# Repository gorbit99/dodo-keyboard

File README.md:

# Dodo

Dodo is a 60%, low-profile, wireless mechanical keyboard with per-key RGB
backlighting a display and a rotary encoder.

## BOM

To build the PCB, you will need the following components for each side (so make
sure to get double of each):

| Part                              | Count | Link                                                                |
| --------------------------------- | ----: | ------------------------------------------------------------------- |
| B5817W Diode                      |     1 | [AliExpress](https://www.aliexpress.com/item/1005005615035910.html) |
| SK6812 MINI-E <sup>1</sup>        |    30 | [AliExpress](https://www.aliexpress.com/item/1005005248164351.html) |
| 1N4148 SOD-123                    |    30 | [AliExpress](https://www.aliexpress.com/item/1005005271390029.html) |
| SMD 3.5 mm jack <sup>2</sup>      |     1 | [AliExpress](https://www.aliexpress.com/item/4000661908135.html)    |
| 2 pin POGO connector <sup>2</sup> |     1 | [AliExpress](https://www.aliexpress.com/item/1005002006325514.html) |
| AO3401A <sup>1</sup>              |     2 | [AliExpress](https://www.aliexpress.com/item/4001197981239.html)    |
| 2N7002 <sup>1</sup>               |     1 | [AliExpress](https://www.aliexpress.com/item/1005004759627915.html) |
| 10k Ω 0603 resistor <sup>1</sup>  |     3 | [AliExpress](https://www.aliexpress.com/item/1005006142628179.html) |
| 560 Ω 0603 resistor <sup>1</sup>  |     2 | [AliExpress](https://www.aliexpress.com/item/1005006142628179.html) |
| Momentary tactile switch          |     2 | [AliExpress](https://www.aliexpress.com/item/1005004159746274.html) |
| EC11E style encoder <sup>3</sup>  |     1 | [AliExpress](https://www.aliexpress.com/item/1005002358274622.html) |
| Kailh Choc V1                     |    30 | [AliExpress](https://www.aliexpress.com/item/1005004522163996.html) |
| XIAO BLE <sup>4</sup>             |     1 | [AliExpress](https://www.aliexpress.com/item/1005004459618789.html) |
| MCP23S17SS                        |     1 | [AliExpress](https://www.aliexpress.com/item/1005004925908454.html) |
| nice!view <sup>5</sup>            |     1 | [Official nice!view site](https://nicekeyboards.com/nice-view/)     |
| SMD JST SH connector              |     1 | [AliExpress](https://www.aliexpress.com/item/1005005682408443.html) |

All links are examples, I recommend looking around for better orders, and
especially switches that you like

1: The following components can be omitted, if you don't want RGB: SK6812
MINI-E, 1xAO3401A, 2N7002, 2x10k resistor, 1x560R resistor

2: These are for power delivery (only!) between the halves, so you can charge
them at the same time, but they are technically optional

3: Optional, if you don't need an encoder

4: You might find these as "XIAO NRF52840" or similar. There is also a sense
variant which is more expensive and not necessary

5: Optional, if you don't need a display

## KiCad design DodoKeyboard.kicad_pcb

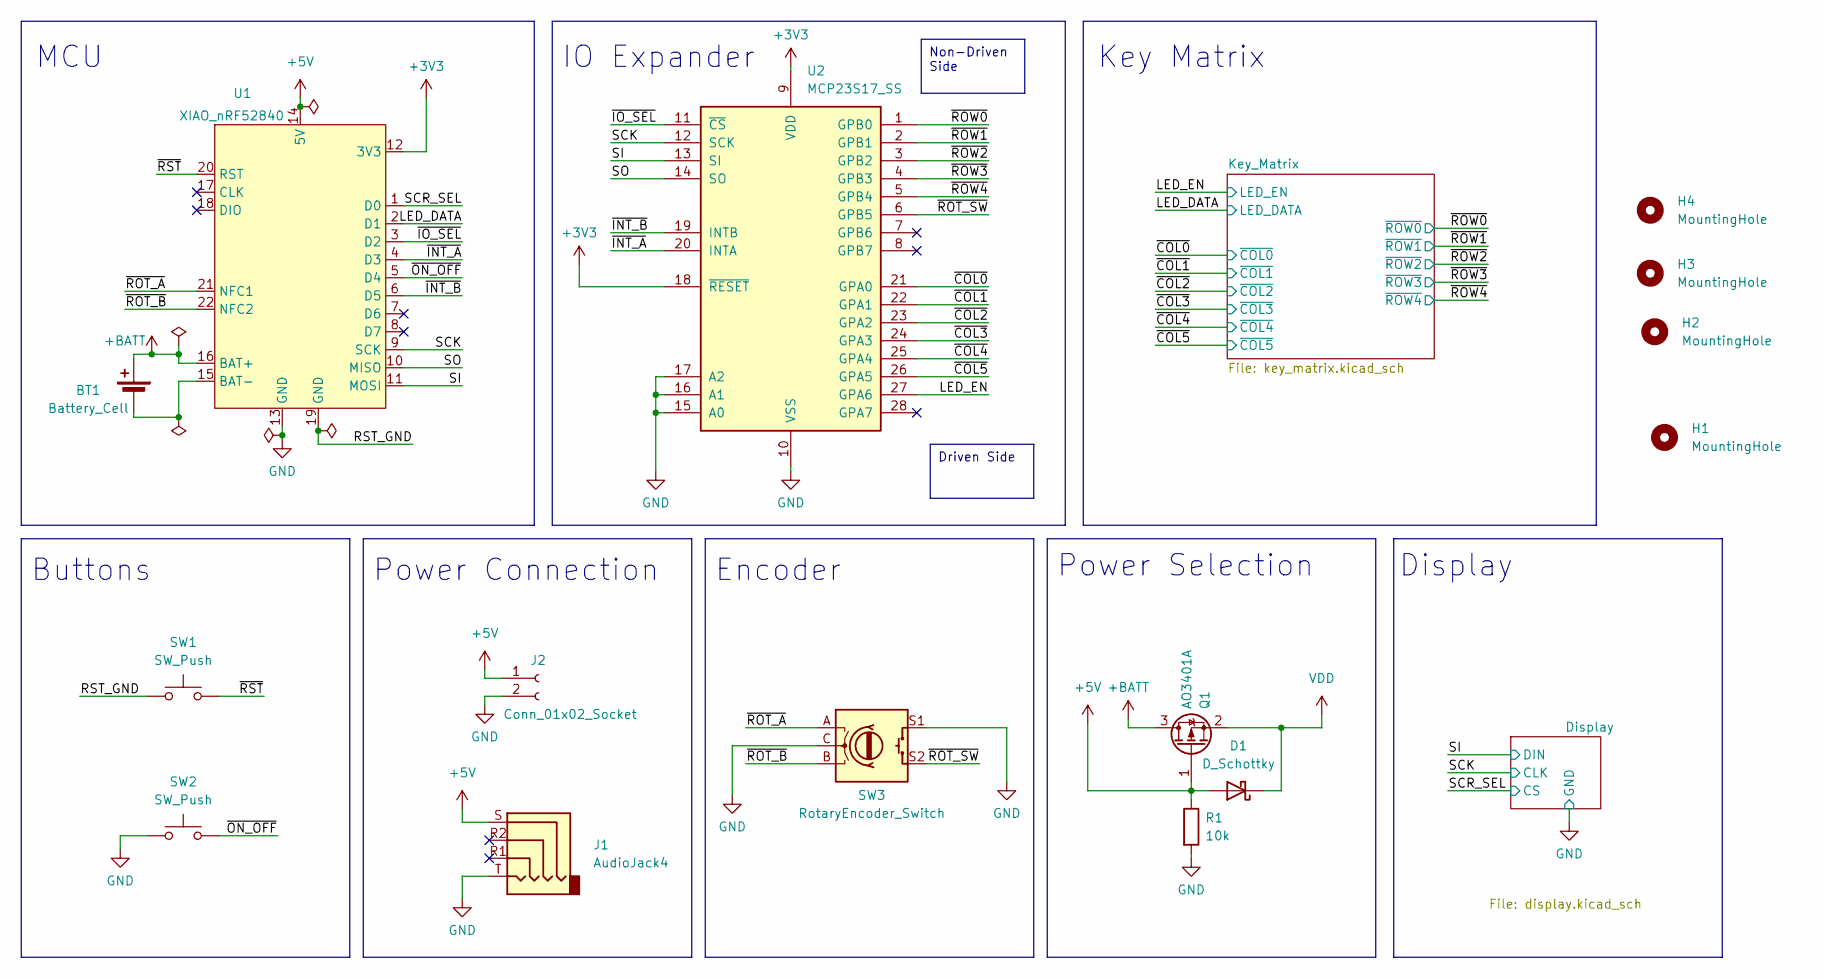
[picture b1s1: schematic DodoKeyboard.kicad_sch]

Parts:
BT1: Battery_Cell; JST_SH_SM02B-SRSS-TB_1x02-1MP_P1.00mm_Horizontal_Double
D1: D_Schottky; D_SOD-123_Double
H1, H2, H3, H4: MountingHole; MountingHole_3.2mm_M3
J1: AudioJack4; Jack_3.5mm_KoreanHropartsElec_PJ-320D-4A_Horizontal_Double
J2: Conn_01x02_Socket; Pogo2-Right-Angle
Q1: AO3401A; SOT-23_Double
R1: 10k; R_0603_1608Metric_Pad0.98x0.95mm_HandSolder_Double
SW1, SW2: SW_Push; SW_PUSH_6mm_Double
SW3: RotaryEncoder_Switch; RotaryEncoder_Alps_EC11E-Switch_Vertical_H20mm_Double
U1: XIAO_nRF52840; XIAO-nRF52840_Double
U2: MCP23S17_SS; SSOP-28_5.3x10.2mm_P0.65mm_Double

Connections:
+3V3: U1.12 (3V3), U2.9 (VDD), U2.18 (~RESET); also elsewhere on the board
+5V: D1.2 (A), J1.S, J2.1, Q1.1 (G), R1.1, U1.14 (5V)
+BATT: BT1.1 (+), Q1.3 (D), U1.16 (BAT+)
/LED_DATA: U1.2 (D1); also elsewhere on the board
/LED_EN: U2.27 (GPA6); also elsewhere on the board
/RST_GND: SW1.1, U1.19 (GND)
/SCK: U1.9 (SCK), U2.12 (SCK); also elsewhere on the board
/SCR_SEL: U1.1 (D0); also elsewhere on the board
/SI: U1.11 (MOSI), U2.13 (SI); also elsewhere on the board
/SO: U1.10 (MISO), U2.14 (SO)
/~COL0: U2.21 (GPA0); also elsewhere on the board
/~COL1: U2.22 (GPA1); also elsewhere on the board
/~COL2: U2.23 (GPA2); also elsewhere on the board
/~COL3: U2.24 (GPA3); also elsewhere on the board
/~COL4: U2.25 (GPA4); also elsewhere on the board
/~COL5: U2.26 (GPA5); also elsewhere on the board
/~INT_A: U1.4 (D3), U2.20 (INTA)
/~INT_B: U1.6 (D5), U2.19 (INTB)
/~IO_SEL: U1.3 (D2), U2.11 (~CS)
/~ON_OFF: SW2.2, U1.5 (D4)
/~ROT_A: SW3.A, U1.21 (NFC1)
/~ROT_B: SW3.B, U1.22 (NFC2)
/~ROT_SW: SW3.S2, U2.6 (GPB5)
/~ROW0: U2.1 (GPB0); also elsewhere on the board
/~ROW1: U2.2 (GPB1); also elsewhere on the board
/~ROW2: U2.3 (GPB2); also elsewhere on the board
/~ROW3: U2.4 (GPB3); also elsewhere on the board
/~ROW4: U2.5 (GPB4); also elsewhere on the board
/~RST: SW1.2, U1.20 (RST)
GND: J1.T, J2.2, R1.2, SW2.1, SW3.C, SW3.S1, U1.13 (GND), U2.10 (VSS), U2.15 (A0), U2.16 (A1), U2.17 (A2); also elsewhere on the board
unnamed: BT1.2 (-), U1.15 (BAT-)
VDD: D1.1 (K), Q1.2 (S); also elsewhere on the board

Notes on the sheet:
Non-Driven Side
Driven Side
Display
Power Connection
Buttons
MCU
Encoder
Key Matrix
Power Selection
IO Expander

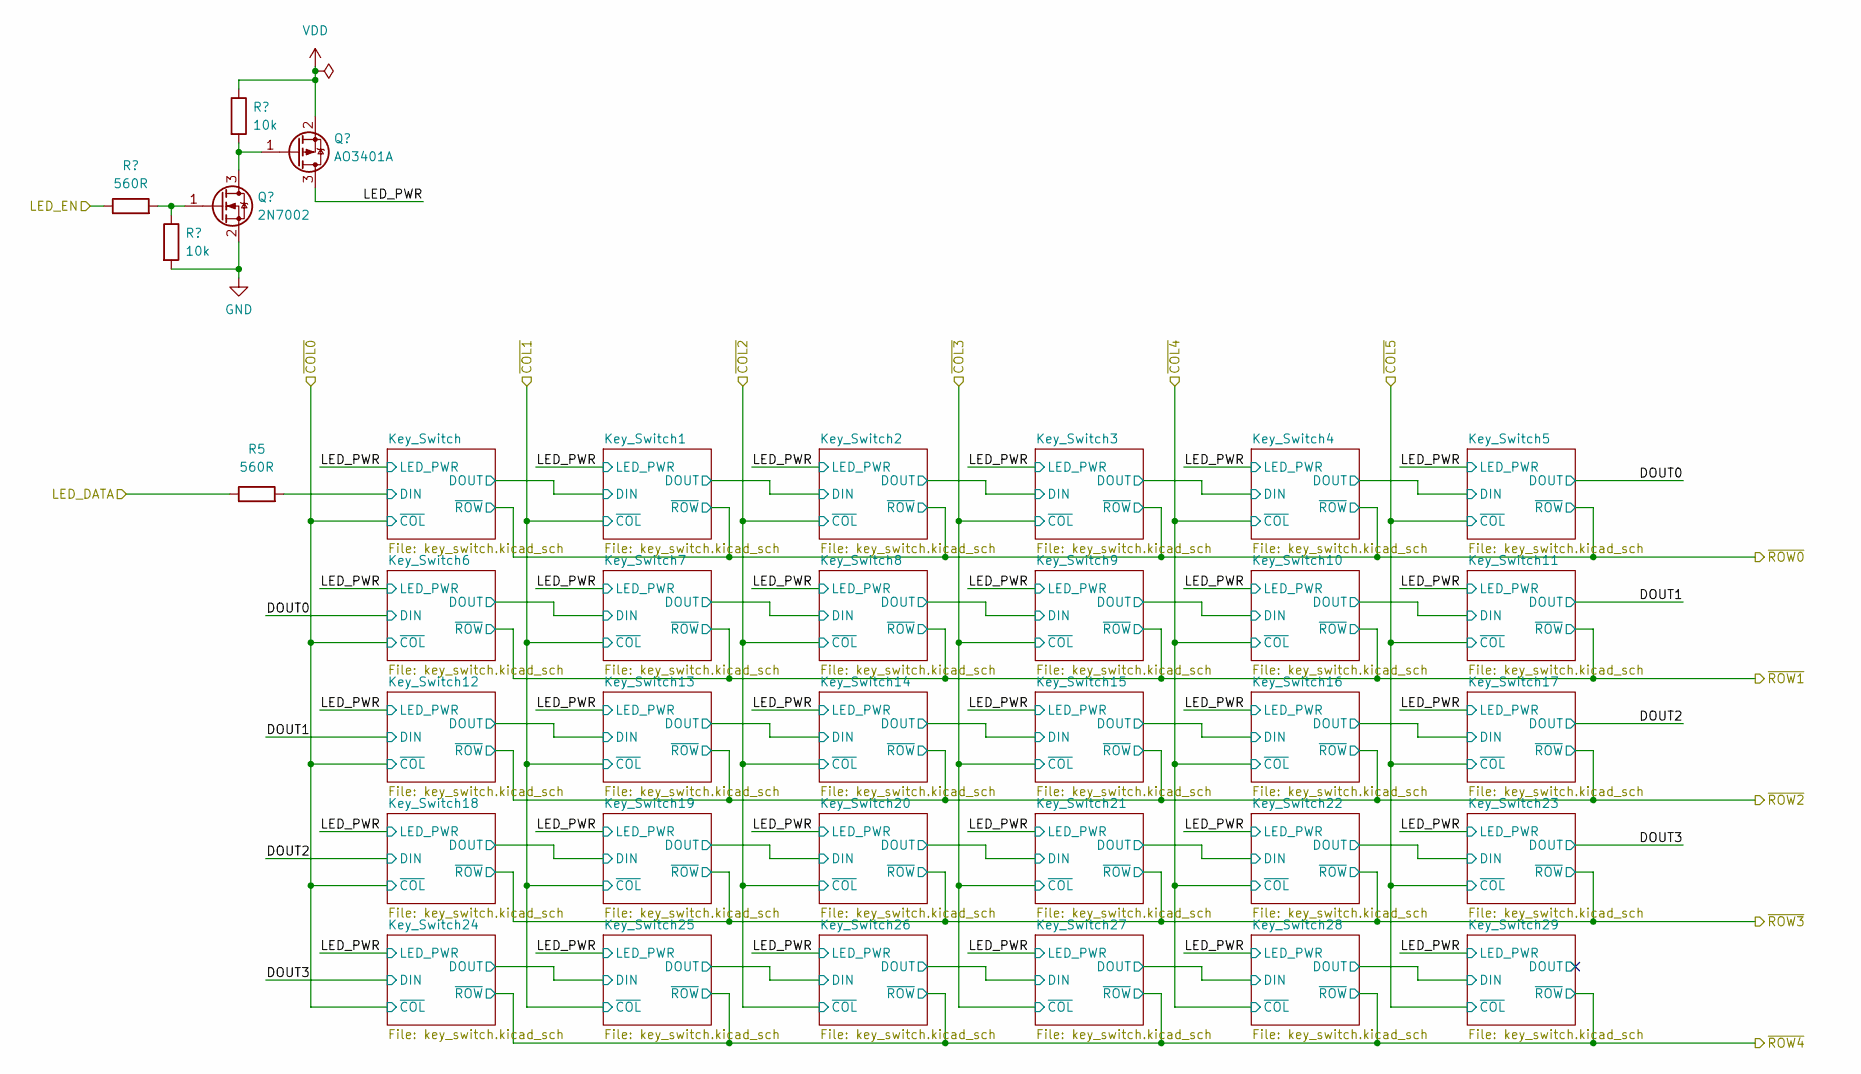
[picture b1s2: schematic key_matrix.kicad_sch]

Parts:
Q3: 2N7002; SOT-23_Double
Q4: AO3401A; SOT-23_Double
R2, R5: 560R; R_0603_1608Metric_Pad0.98x0.95mm_HandSolder_Double
R3, R4: 10k; R_0603_1608Metric_Pad0.98x0.95mm_HandSolder_Double

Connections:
/Key_Matrix/Key_Switch/DIN: R5.2; also elsewhere on the board
/Key_Matrix/LED_PWR: Q4.3 (D); also elsewhere on the board
/LED_DATA: R5.1; also elsewhere on the board
/LED_EN: R2.1; also elsewhere on the board
GND: Q3.2 (S), R3.2; also elsewhere on the board
unnamed: Q3.3 (D), Q4.1 (G), R4.2
unnamed: Q3.1 (G), R2.2, R3.1
VDD: Q4.2 (S), R4.1; also elsewhere on the board

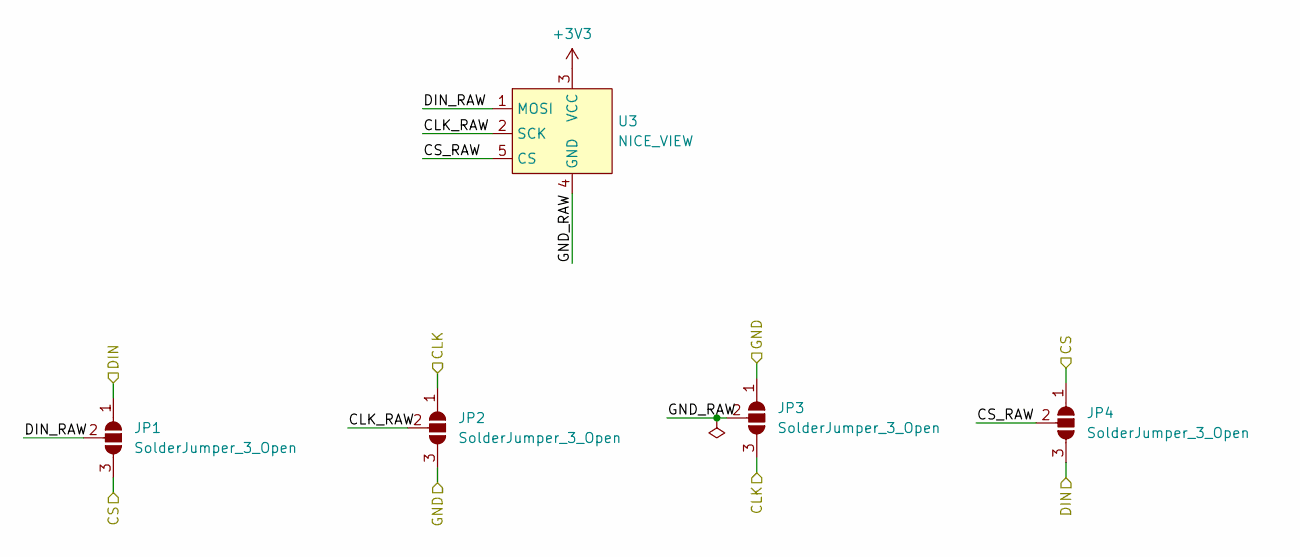
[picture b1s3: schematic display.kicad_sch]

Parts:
JP1, JP2, JP3, JP4: SolderJumper_3_Open; Double_Sided_Jumper
U3: NICE_VIEW

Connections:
+3V3: U3.3 (VCC); also elsewhere on the board
/Display/CLK_RAW: JP2.2 (C), U3.2 (SCK)
/Display/CS_RAW: JP4.2 (C), U3.5 (CS)
/Display/DIN_RAW: JP1.2 (C), U3.1 (MOSI)
/Display/GND_RAW: JP3.2 (C), U3.4 (GND)
/SCK: JP2.1 (A), JP3.3 (B); also elsewhere on the board
/SCR_SEL: JP1.3 (B), JP4.1 (A); also elsewhere on the board
/SI: JP1.1 (A), JP4.3 (B); also elsewhere on the board
GND: JP2.3 (B), JP3.1 (A); also elsewhere on the board

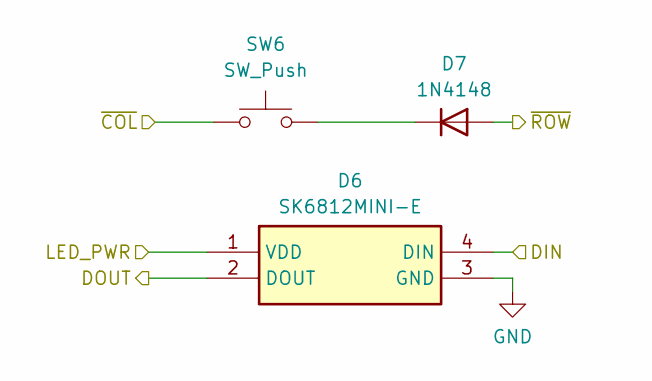
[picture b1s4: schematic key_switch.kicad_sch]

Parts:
D6: SK6812MINI-E; SK6812MINI-E_Double; Manufacturer_Part_Number SK6812MINI-E
D7: 1N4148; D_SOD-123_Double
SW6: SW_Push; SW_Kailh_Choc_V1_1.00u_Double

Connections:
/Key_Matrix/Key_Switch1/DOUT: D6.4 (DIN); also elsewhere on the board
/Key_Matrix/Key_Switch2/DOUT: D6.2 (DOUT); also elsewhere on the board
/Key_Matrix/LED_PWR: D6.1 (VDD); also elsewhere on the board
/~COL2: SW6.1; also elsewhere on the board
/~ROW0: D7.2 (A); also elsewhere on the board
GND: D6.3 (GND); also elsewhere on the board
unnamed: D7.1 (K), SW6.2

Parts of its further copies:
D2, D4, D8, D10, D12, D14, D16, D18, D20, D22, D24, D26, D28, D30, D32, D34, D36, D38, D40, D42, D44, D46, D48, D50, D52, D54, D56, D58, D60: SK6812MINI-E; SK6812MINI-E_Double; Manufacturer_Part_Number SK6812MINI-E
D3, D5, D9, D11, D13, D15, D17, D19, D21, D23, D25, D27, D29, D31, D33, D35, D37, D39, D41, D43, D45, D47, D49, D51, D53, D55, D57, D59, D61: 1N4148; D_SOD-123_Double
SW4, SW5, SW7, SW8, SW9, SW10, SW11, SW12, SW13, SW14, SW15, SW16, SW17, SW18, SW19, SW20, SW21, SW22, SW23, SW24, SW25, SW26, SW27, SW28, SW29, SW30, SW31, SW32, SW33: SW_Push; SW_Kailh_Choc_V1_1.00u_Double

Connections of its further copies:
/Key_Matrix/DOUT0: D12.2 (DOUT), D14.4 (DIN)
/Key_Matrix/DOUT1: D24.2 (DOUT), D26.4 (DIN)
/Key_Matrix/DOUT2: D36.2 (DOUT), D38.4 (DIN)
/Key_Matrix/DOUT3: D48.2 (DOUT), D50.4 (DIN)
/Key_Matrix/Key_Switch1/DOUT: D4.2 (DOUT); also elsewhere on the board
/Key_Matrix/Key_Switch2/DOUT: D8.4 (DIN); also elsewhere on the board
/Key_Matrix/Key_Switch3/DOUT: D8.2 (DOUT), D10.4 (DIN)
/Key_Matrix/Key_Switch4/DOUT: D10.2 (DOUT), D12.4 (DIN)
/Key_Matrix/Key_Switch6/DOUT: D14.2 (DOUT), D16.4 (DIN)
/Key_Matrix/Key_Switch7/DOUT: D16.2 (DOUT), D18.4 (DIN)
/Key_Matrix/Key_Switch8/DOUT: D18.2 (DOUT), D20.4 (DIN)
/Key_Matrix/Key_Switch10/DIN: D20.2 (DOUT), D22.4 (DIN)
/Key_Matrix/Key_Switch10/DOUT: D22.2 (DOUT), D24.4 (DIN)
/Key_Matrix/Key_Switch12/DOUT: D26.2 (DOUT), D28.4 (DIN)
/Key_Matrix/Key_Switch13/DOUT: D28.2 (DOUT), D30.4 (DIN)
/Key_Matrix/Key_Switch14/DOUT: D30.2 (DOUT), D32.4 (DIN)
/Key_Matrix/Key_Switch15/DOUT: D32.2 (DOUT), D34.4 (DIN)
/Key_Matrix/Key_Switch16/DOUT: D34.2 (DOUT), D36.4 (DIN)
/Key_Matrix/Key_Switch18/DOUT: D38.2 (DOUT), D40.4 (DIN)
/Key_Matrix/Key_Switch19/DOUT: D40.2 (DOUT), D42.4 (DIN)
/Key_Matrix/Key_Switch20/DOUT: D42.2 (DOUT), D44.4 (DIN)
/Key_Matrix/Key_Switch21/DOUT: D44.2 (DOUT), D46.4 (DIN)
/Key_Matrix/Key_Switch22/DOUT: D46.2 (DOUT), D48.4 (DIN)
/Key_Matrix/Key_Switch24/DOUT: D50.2 (DOUT), D52.4 (DIN)
/Key_Matrix/Key_Switch25/DOUT: D52.2 (DOUT), D54.4 (DIN)
/Key_Matrix/Key_Switch26/DOUT: D54.2 (DOUT), D56.4 (DIN)
/Key_Matrix/Key_Switch27/DOUT: D56.2 (DOUT), D58.4 (DIN)
/Key_Matrix/Key_Switch28/DOUT: D58.2 (DOUT), D60.4 (DIN)
/Key_Matrix/Key_Switch29/DOUT: D60.2 (DOUT)
/Key_Matrix/Key_Switch/DIN: D2.4 (DIN); also elsewhere on the board
/Key_Matrix/Key_Switch/DOUT: D2.2 (DOUT), D4.4 (DIN)
/Key_Matrix/LED_PWR: D2.1 (VDD), D4.1 (VDD), D8.1 (VDD), D10.1 (VDD), D12.1 (VDD), D14.1 (VDD), D16.1 (VDD), D18.1 (VDD), D20.1 (VDD), D22.1 (VDD), D24.1 (VDD), D26.1 (VDD), D28.1 (VDD), D30.1 (VDD), D32.1 (VDD), D34.1 (VDD), D36.1 (VDD), D38.1 (VDD), D40.1 (VDD), D42.1 (VDD), D44.1 (VDD), D46.1 (VDD), D48.1 (VDD), D50.1 (VDD), D52.1 (VDD), D54.1 (VDD), D56.1 (VDD), D58.1 (VDD), D60.1 (VDD); also elsewhere on the board
/~COL0: SW4.1, SW10.1, SW16.1, SW22.1, SW28.1; also elsewhere on the board
/~COL1: SW5.1, SW11.1, SW17.1, SW23.1, SW29.1; also elsewhere on the board
/~COL2: SW12.1, SW18.1, SW24.1, SW30.1; also elsewhere on the board
/~COL3: SW7.1, SW13.1, SW19.1, SW25.1, SW31.1; also elsewhere on the board
/~COL4: SW8.1, SW14.1, SW20.1, SW26.1, SW32.1; also elsewhere on the board
/~COL5: SW9.1, SW15.1, SW21.1, SW27.1, SW33.1; also elsewhere on the board
/~ROW0: D3.2 (A), D5.2 (A), D9.2 (A), D11.2 (A), D13.2 (A); also elsewhere on the board
/~ROW1: D15.2 (A), D17.2 (A), D19.2 (A), D21.2 (A), D23.2 (A), D25.2 (A); also elsewhere on the board
/~ROW2: D27.2 (A), D29.2 (A), D31.2 (A), D33.2 (A), D35.2 (A), D37.2 (A); also elsewhere on the board
/~ROW3: D39.2 (A), D41.2 (A), D43.2 (A), D45.2 (A), D47.2 (A), D49.2 (A); also elsewhere on the board
/~ROW4: D51.2 (A), D53.2 (A), D55.2 (A), D57.2 (A), D59.2 (A), D61.2 (A); also elsewhere on the board
GND: D2.3 (GND), D4.3 (GND), D8.3 (GND), D10.3 (GND), D12.3 (GND), D14.3 (GND), D16.3 (GND), D18.3 (GND), D20.3 (GND), D22.3 (GND), D24.3 (GND), D26.3 (GND), D28.3 (GND), D30.3 (GND), D32.3 (GND), D34.3 (GND), D36.3 (GND), D38.3 (GND), D40.3 (GND), D42.3 (GND), D44.3 (GND), D46.3 (GND), D48.3 (GND), D50.3 (GND), D52.3 (GND), D54.3 (GND), D56.3 (GND), D58.3 (GND), D60.3 (GND); also elsewhere on the board
unnamed: D3.1 (K), SW4.2
unnamed: D5.1 (K), SW5.2
unnamed: D9.1 (K), SW7.2
unnamed: D11.1 (K), SW8.2
unnamed: D13.1 (K), SW9.2
unnamed: D15.1 (K), SW10.2
unnamed: D17.1 (K), SW11.2
unnamed: D19.1 (K), SW12.2
unnamed: D21.1 (K), SW13.2
unnamed: D23.1 (K), SW14.2
unnamed: D25.1 (K), SW15.2
unnamed: D27.1 (K), SW16.2
unnamed: D29.1 (K), SW17.2
unnamed: D31.1 (K), SW18.2
unnamed: D33.1 (K), SW19.2
unnamed: D35.1 (K), SW20.2
unnamed: D37.1 (K), SW21.2
unnamed: D39.1 (K), SW22.2
unnamed: D41.1 (K), SW23.2
unnamed: D43.1 (K), SW24.2
unnamed: D45.1 (K), SW25.2
unnamed: D47.1 (K), SW26.2
unnamed: D49.1 (K), SW27.2
unnamed: D51.1 (K), SW28.2
unnamed: D53.1 (K), SW29.2
unnamed: D55.1 (K), SW30.2
unnamed: D57.1 (K), SW31.2
unnamed: D59.1 (K), SW32.2
unnamed: D61.1 (K), SW33.2

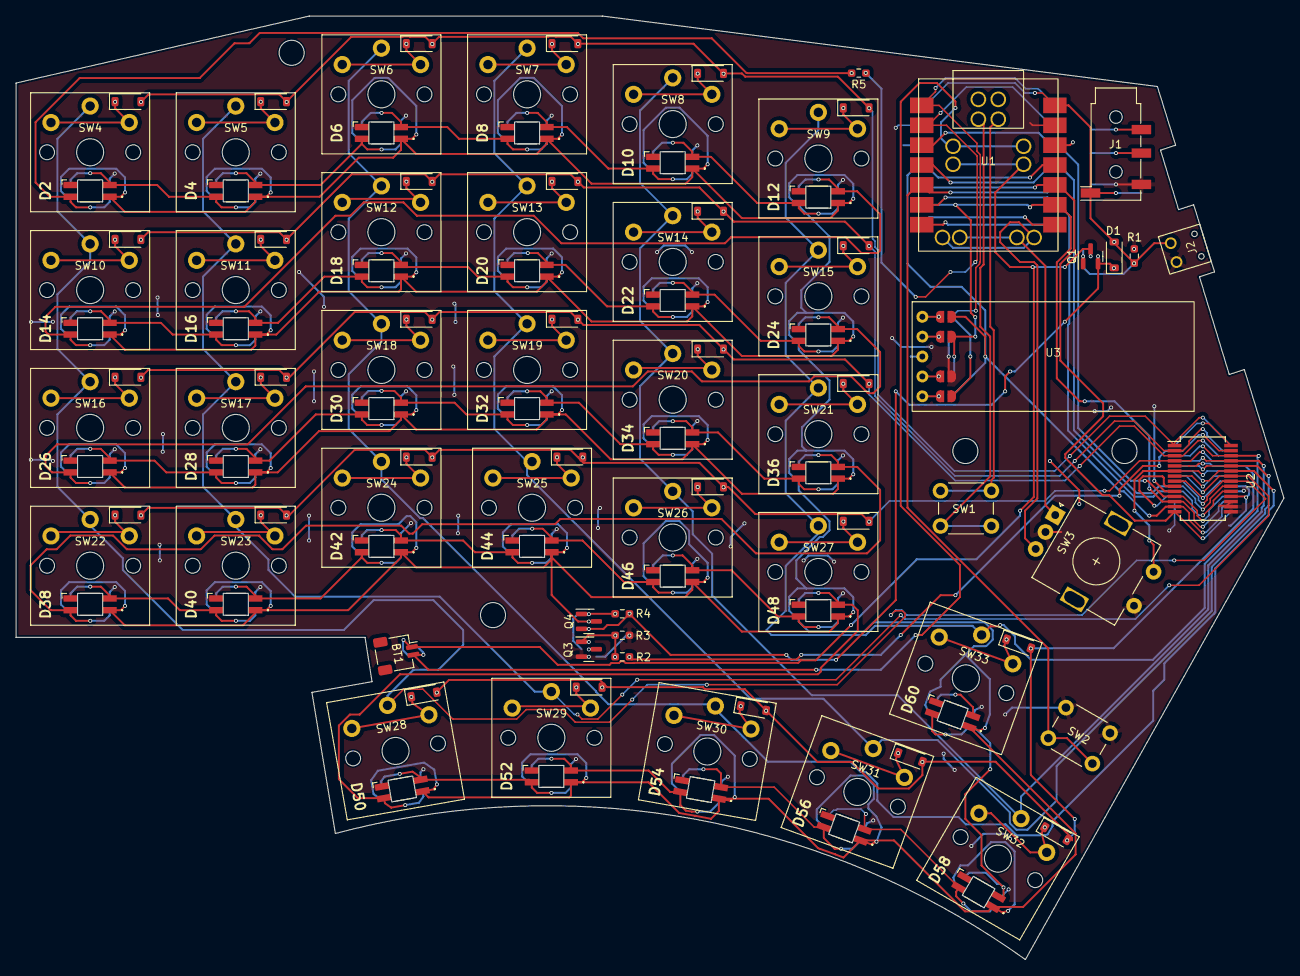
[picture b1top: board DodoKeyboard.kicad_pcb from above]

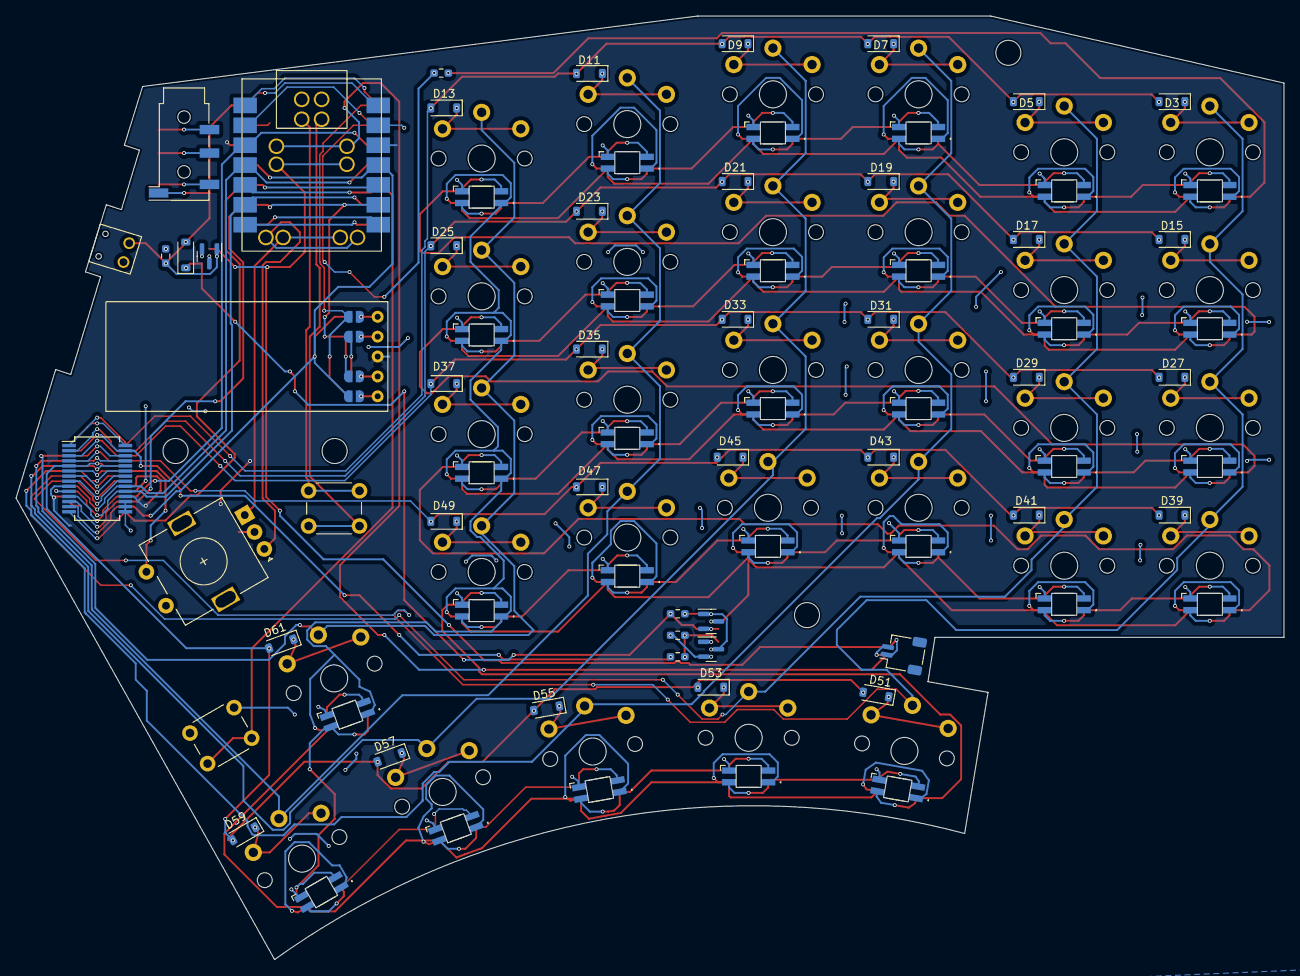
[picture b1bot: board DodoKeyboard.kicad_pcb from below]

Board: 2 copper layers, 161.9 x 120.5 mm, 116 parts (30 on the bottom side), 99 nets.

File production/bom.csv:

Designator,Footprint,Quantity,Value,LCSC Part #
BT1,JST_SH_SM02B-SRSS-TB_1x02-1MP_P1.00mm_Horizontal_Double,1,Battery_Cell,
D1,D_SOD-123_Double,1,D_Schottky,
"D10, D12, D14, D16, D18, D2, D20, D22, D24, D26, D28, D30, D32, D34, D36, D38, D4, D40, D42, D44, D46, D48, D50, D52, D54, D56, D58, D6, D60, D8",SK6812MINI-E_Double,30,SK6812MINI-E,
"D11, D13, D15, D17, D19, D21, D23, D25, D27, D29, D3, D31, D33, D35, D37, D39, D41, D43, D45, D47, D49, D5, D51, D53, D55, D57, D59, D61, D7, D9",D_SOD-123_Double,30,1N4148,
"H1, H2, H3, H4",MountingHole_3.2mm_M3,4,MountingHole,
J1,Jack_3.5mm_KoreanHropartsElec_PJ-320D-4A_Horizontal_Double,1,AudioJack4,
J2,Pogo2-Right-Angle,1,Conn_01x02_Socket,
"JP1, JP2, JP3, JP4",Double_Sided_Jumper,4,SolderJumper_3_Open,
"Q1, Q4",SOT-23_Double,2,AO3401A,
Q3,SOT-23_Double,1,2N7002,
"R1, R3, R4",0603,3,10k,
"R2, R5",0603,2,560R,
"SW1, SW2",SW_PUSH_6mm_Double,2,SW_Push,
"SW10, SW11, SW12, SW13, SW14, SW15, SW16, SW17, SW18, SW19, SW20, SW21, SW22, SW23, SW24, SW25, SW26, SW27, SW28, SW29, SW30, SW31, SW32, SW33, SW4, SW5, SW6, SW7, SW8, SW9",SW_Kailh_Choc_V1_1.00u_Double,30,SW_Push,
SW3,RotaryEncoder_Alps_EC11E-Switch_Vertical_H20mm_Double,1,RotaryEncoder_Switch,
U1,XIAO-nRF52840_Double,1,XIAO_nRF52840,
U2,SSOP-28_5.3x10.2mm_P0.65mm_Double,1,MCP23S17_SS,
U3,NICE_VIEW,1,NICE_VIEW,

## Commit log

2023-12-22 Initial
2023-12-22 README
2023-12-22 Better 3D render
2023-12-22 Actually better 3d render this time
2023-12-22 Case
2023-12-22 Added JST SH to BOM
2023-12-22 Update gitignore
